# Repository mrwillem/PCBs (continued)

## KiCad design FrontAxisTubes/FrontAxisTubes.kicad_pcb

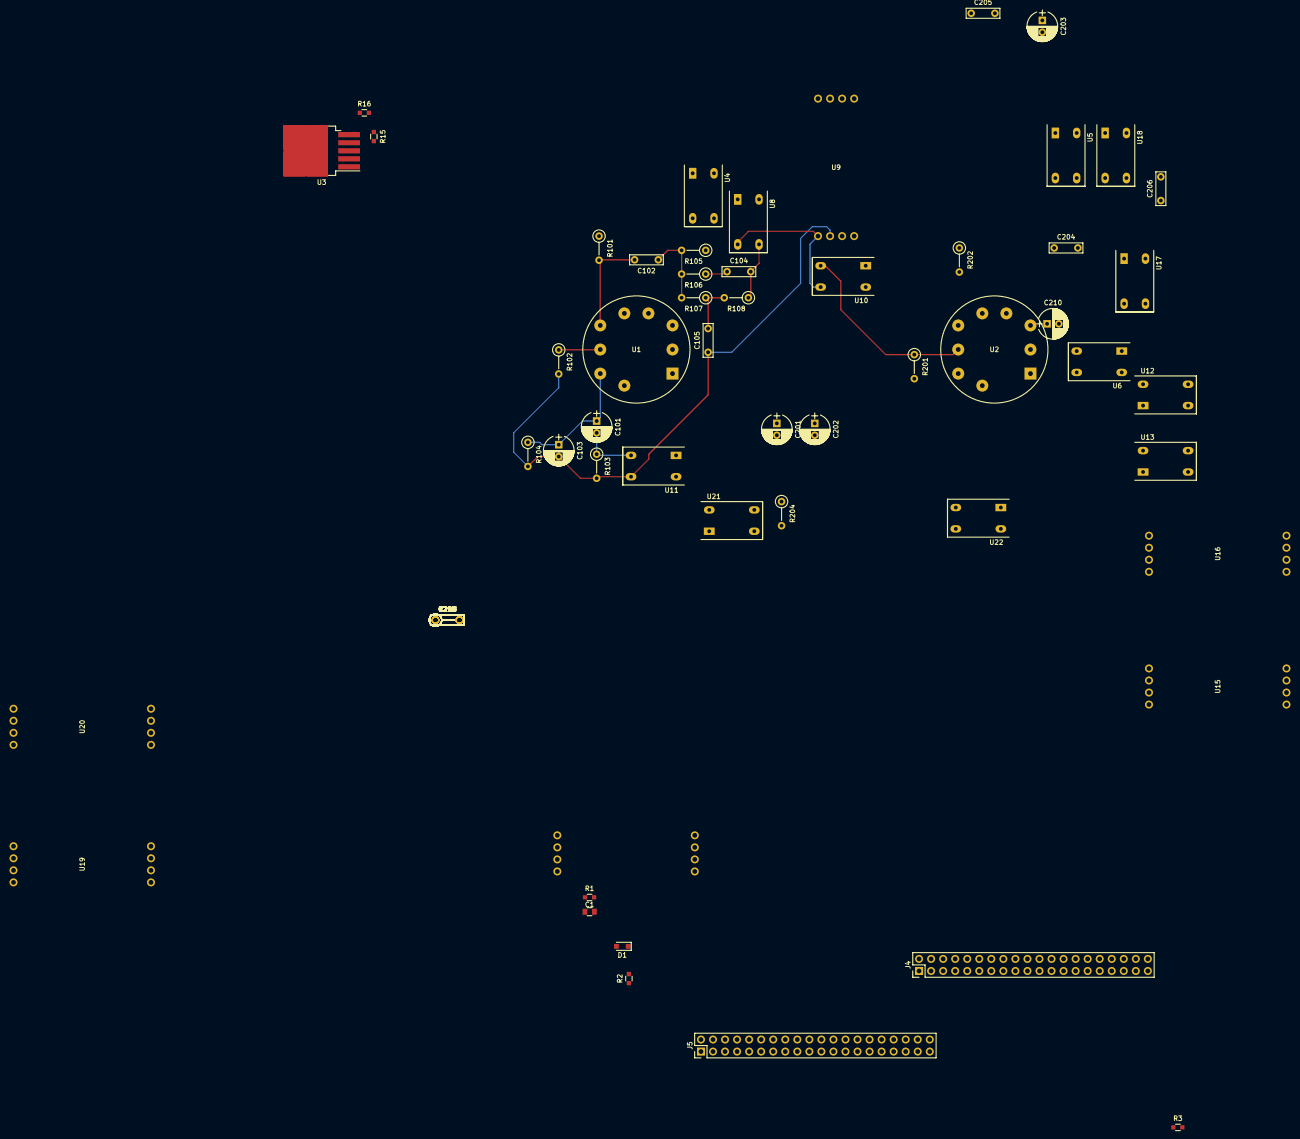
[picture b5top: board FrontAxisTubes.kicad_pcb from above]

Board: 2 copper layers, 65 parts (1 on the bottom side), 44 nets.

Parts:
C1: 47 uF; C_0805
C101, C201, C203, C210: 15uF; CP_Radial_D6.3mm_P2.50mm
C102: 20nF; C_Rect_L7.0mm_W2.0mm_P5.00mm
C103: 1uF; CP_Radial_D6.3mm_P2.50mm
C104: 1nF; C_Rect_L7.0mm_W2.0mm_P5.00mm
C105: 47pF; C_Rect_L7.0mm_W2.0mm_P5.00mm
C202: 47uF; CP_Radial_D6.3mm_P2.50mm
C204: 750pF; C_Rect_L7.0mm_W2.0mm_P5.00mm
C205: 250pF; C_Rect_L7.0mm_W2.0mm_P5.00mm
C206: 100nF; C_Rect_L7.0mm_W2.0mm_P5.00mm
C207: 47nF; C_Rect_L7.0mm_W2.0mm_P5.00mm
C208: 75pF; C_Rect_L7.0mm_W2.0mm_P5.00mm
C209: 120pF; C_Rect_L7.0mm_W2.0mm_P5.00mm
D1: D; D_SOD-323_HandSoldering
J4, J5: CONN_02X20; Pin_Header_Straight_2x20_Pitch2.54mm
R1: 6,8K; R_0603_HandSolder
R2, R3: 3,3K; R_0603_HandSolder
R15: 36K1 PAT0603E3612BST5; R_0603_HandSolder
R16: 3K9 CPF0603B3K9E1; R_0603_HandSolder
R101, R208, R211: 100K; R_Axial_DIN0207_L6.3mm_D2.5mm_P5.08mm_Vertical
R102, R201: 1M; R_Axial_DIN0207_L6.3mm_D2.5mm_P5.08mm_Vertical
R103, R203, R205: 22K; R_Axial_DIN0207_L6.3mm_D2.5mm_P5.08mm_Vertical
R104, R204, R212: 1K5; R_Axial_DIN0207_L6.3mm_D2.5mm_P5.08mm_Vertical
R105: 270K; R_Axial_DIN0207_L6.3mm_D2.5mm_P5.08mm_Vertical
R106, R206: 82K; R_Axial_DIN0207_L6.3mm_D2.5mm_P5.08mm_Vertical
R107: 470K; R_Axial_DIN0207_L6.3mm_D2.5mm_P5.08mm_Vertical
R108: 330K; R_Axial_DIN0207_L6.3mm_D2.5mm_P5.08mm_Vertical
R202: 150K; R_Axial_DIN0207_L6.3mm_D2.5mm_P5.08mm_Vertical
R207, R209, R210: 10M; R_Axial_DIN0207_L6.3mm_D2.5mm_P5.08mm_Vertical
U1, U2: ECC83; VALVE-NOVAL_P
U3: TL1963A-Q1; TO-263-5_TabPin6
U4, U5, U6, U8, U10, U11, U12, U13, U17, U18, U21, U22: LDRSWITCH; Optoisolator_LCR-0202
U7, U9, U15, U16, U19, U20: Dual_LDR_Modul; Dual_LDR_Module

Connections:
12V6: R15.2, U1.4, U2.4, U3.4
+3V3: U4.2, U8.2, U12.2, U13.2
+420V: R101.1, R202.1, R211.1
GAIN2: C209.1, R210.1, U2.2, U6.4, U20.6, U20.7
GNDD: U15.4, U16.4, U20.4
GND_V1: C103.2, C105.1, R102.2, R103.2, R104.2, U9.6, U11.3
GND_V2: C210.2, R201.2, R207.1, R212.1, U17.3, U19.8, U20.8
HEATER_GND: R16.1, U1.5, U2.5, U3.3
unnamed: C1.1, D1.1
unnamed: R211.2, U2.1
unnamed: U3.1, U3.2
unnamed: U15.5, U16.8
unnamed: U16.6, U16.7
unnamed: C101.1, C103.1, R104.1, U1.8
unnamed: C101.2, R103.1, U11.4
unnamed: C102.1, R105.2, R106.2, R107.2
unnamed: C102.2, R101.2, U1.6
unnamed: C104.1, R106.1
unnamed: C104.2, R108.1, U8.3
unnamed: C105.2, R107.1, R108.2
unnamed: C201.1, C202.1, R204.1, U2.8
unnamed: C201.2, R203.1, U21.4
unnamed: C202.2, R205.1, U22.3
unnamed: C203.1, C204.2, C205.2, R206.1, R208.1, U18.4
unnamed: C203.2, R207.2, U17.4
unnamed: C204.1, R209.2, U5.3
unnamed: C205.1, R209.1, U5.4, U7.5
unnamed: C206.1, U7.8, U19.5
unnamed: C206.2, C207.2, R208.2, U18.3
unnamed: C207.1, U19.6, U19.7
unnamed: C208.1, R210.2, U6.3
unnamed: C210.1, R212.2, U2.3
unnamed: U12.4, U13.4
unnamed: R15.1, R16.2, U3.5
unnamed: R102.1, U1.7
unnamed: R105.1, U4.3
unnamed: R202.2, R206.2, U2.6
unnamed: R203.2, R204.2, R205.2, U21.3
unnamed: U4.4, U8.4, U9.5, U10.3
unnamed: U15.6, U15.7
SW1: J4.1, U12.1
SW2: J4.2, U13.1
TONE1_OUT: C208.2, C209.2, U7.6, U7.7, U20.5
TO_V2A: R201.1, U2.7, U10.4, U13.3

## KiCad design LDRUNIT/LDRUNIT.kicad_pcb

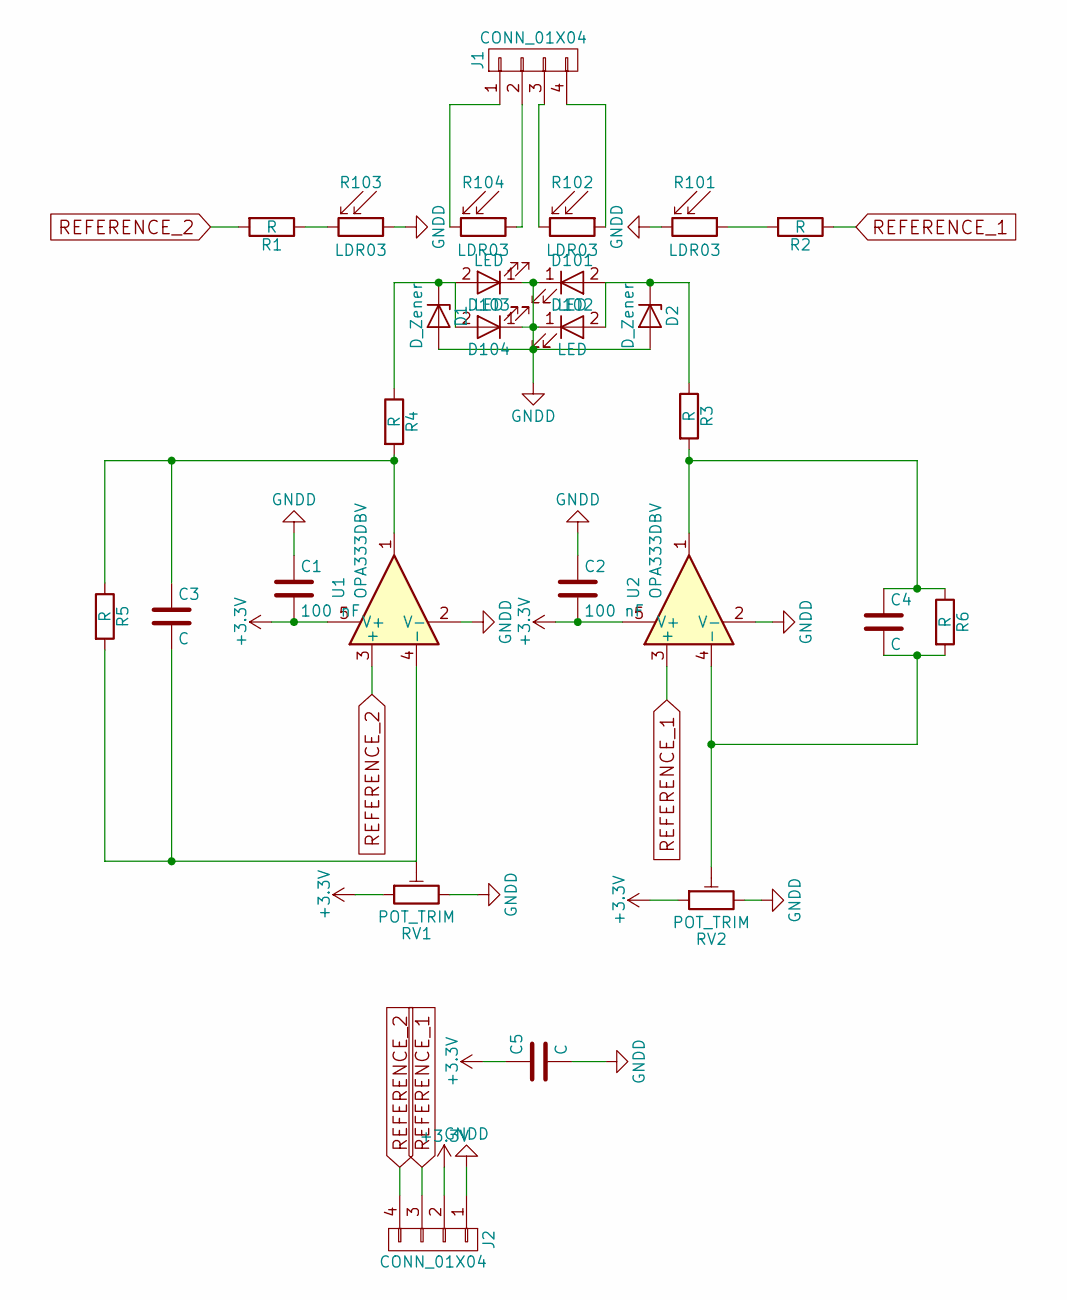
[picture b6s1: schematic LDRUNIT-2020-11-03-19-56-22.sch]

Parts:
C1, C2: 100 nF; R_0603_HandSolder
C3, C4, C5: C; R_0805_HandSolder
D1, D2: D_Zener; D_SOD-123
D101, D103: LED; LED_1206_HandSoldering
D102, D104: LED; LED_D3.0mm
J1, J2: CONN_01X04; Pin_Header__1x04_Pitch2.54mm
R1, R2, R3, R4, R5, R6: R; R_0805_HandSolder
R101, R102, R103, R104: LDR03; Resistor_LDR_5.1x4.3_RM3.4
RV1, RV2: POT_TRIM; Potentiometer_Trimmer_Bourns_3224J
U1, U2: OPA333DBV; SOT-23-5

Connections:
+3V3: C1.2, C2.2, C5.1, J2.2, RV1.1, RV2.1, U1.5 (V+), U2.5 (V+)
GNDD: C1.1, C2.1, C5.2, D1.2 (A), D2.2 (A), D101.1 (K), D102.1 (K), D103.1 (K), D104.1 (K), J2.1, R101.2, R103.1, RV1.3, RV2.3, U1.2 (V-), U2.2 (V-)
unnamed: C3.1, R4.2, R5.1, U1.1
unnamed: C3.2, R5.2, RV1.2, U1.4 (-)
unnamed: C4.1, R3.2, R6.1, U2.1
unnamed: C4.2, R6.2, RV2.2, U2.4 (-)
unnamed: D1.1 (K), D103.2 (A), D104.2 (A), R4.1
unnamed: D2.1 (K), D101.2 (A), D102.2 (A), R3.1
unnamed: J1.1, R104.2
unnamed: J1.2, R104.1
unnamed: J1.3, R102.2
unnamed: J1.4, R102.1
unnamed: R1.1, R103.2
unnamed: R2.2, R101.1
REFERENCE_1: J2.3, R2.1, U2.3 (+)
REFERENCE_2: J2.4, R1.2, U1.3 (+)

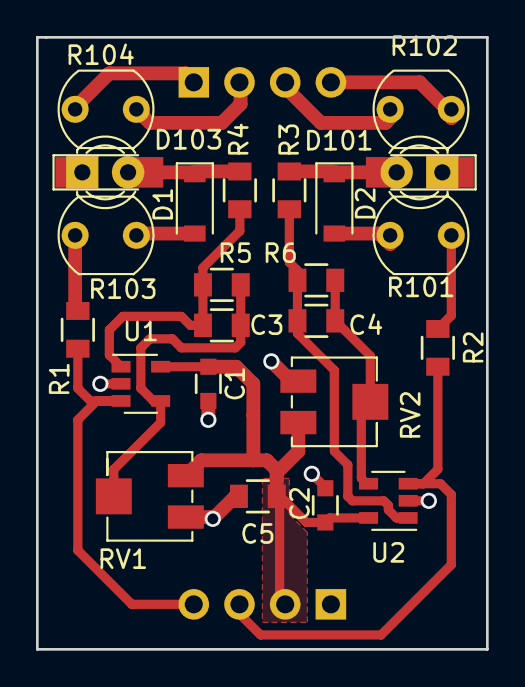
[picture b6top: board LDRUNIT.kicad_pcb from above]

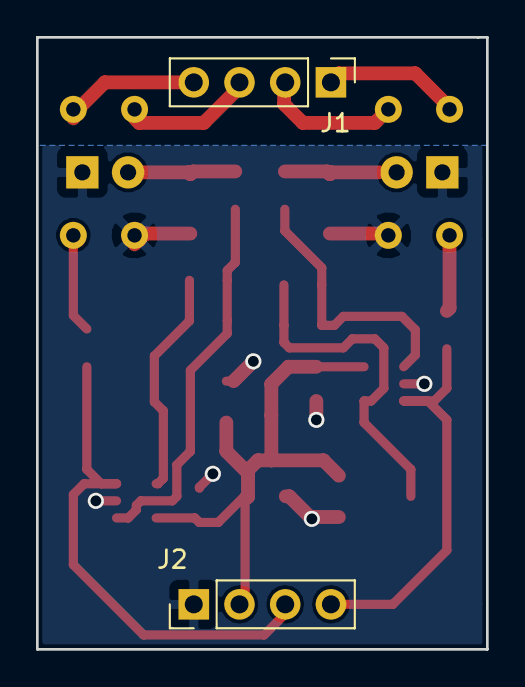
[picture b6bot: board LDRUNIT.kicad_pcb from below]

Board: 2 copper layers, 25.0 x 34.0 mm, 27 parts (2 on the bottom side), 16 nets.
